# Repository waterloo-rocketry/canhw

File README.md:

## RocketCAN Hardware

This repository tracks the hardware development for the RocketCAN project. All schematics, board designs, and fabrication files are tracked in this repository. The corresponding software running on each board can be found in the `cansw_*` repositories. The CAN driver library used is tracked in the `canlib` repository.

All hardware files were developed in KiCAD.

### System Architecture

The RocketCAN project is an extension of the 2018 Flight Instrumentation project. The functions of the original Flight Instrumentation electronics are decoupled into several single-function modules connected by a Controller Area Network (CAN bus). The 2019 RocketCAN configuration consists of a radio board, an injector valve driver, a vent valve driver, a flight sensor suite, a system logger, and a GPS receiver. The modules freely share information over the CAN bus, allowing all modules to access resources such as the radio transceiver and sensor module. This minimizes the amount of component and functionality duplication, as well as power consumption (especially by the radio module). Power consumption is reduced further by allowing the radio board to control power to the rest of the system, forcing it into a low-power state while the rocket is idle. The resulting PCBs are also significantly smaller and easier to mount inside the rocket. Finally, RocketCAN’s configuration is easily extensible. A new subsystem simply needs to include a CAN communication module, after which it can communicate with all other boards on the bus. Potential extensions such as a flight computer, a state estimation module, or an air braking system would be able to use existing sensor data without implementing their own independent sensor suite.

At present, the radio board integrates with Waterloo Rocketry's Remote Launch Control System (RLCS), from which it receives instructions. It is also capable of broadcasting sensor data to RLCS.  The radio board communicates with the tower-side box of RLCS, which relays the data to the client-side box at mission control.

The CAN protocol was chosen for its high data rate, priority-based arbitration, and abundance of inexpensive hardware. The bus can safely be used by many boards at once without the risk of a low-priority message (eg. sensor data) preempting a high-priority message (eg. valve command). Microcontrollers with CAN modules, stand-alone CAN modules, and CAN transceivers are all widely available, making it cheap and simple to add CAN functionality to a subsystem.

Further descriptions and instructions for using each individual board are available in the README in the relevant board's directory.

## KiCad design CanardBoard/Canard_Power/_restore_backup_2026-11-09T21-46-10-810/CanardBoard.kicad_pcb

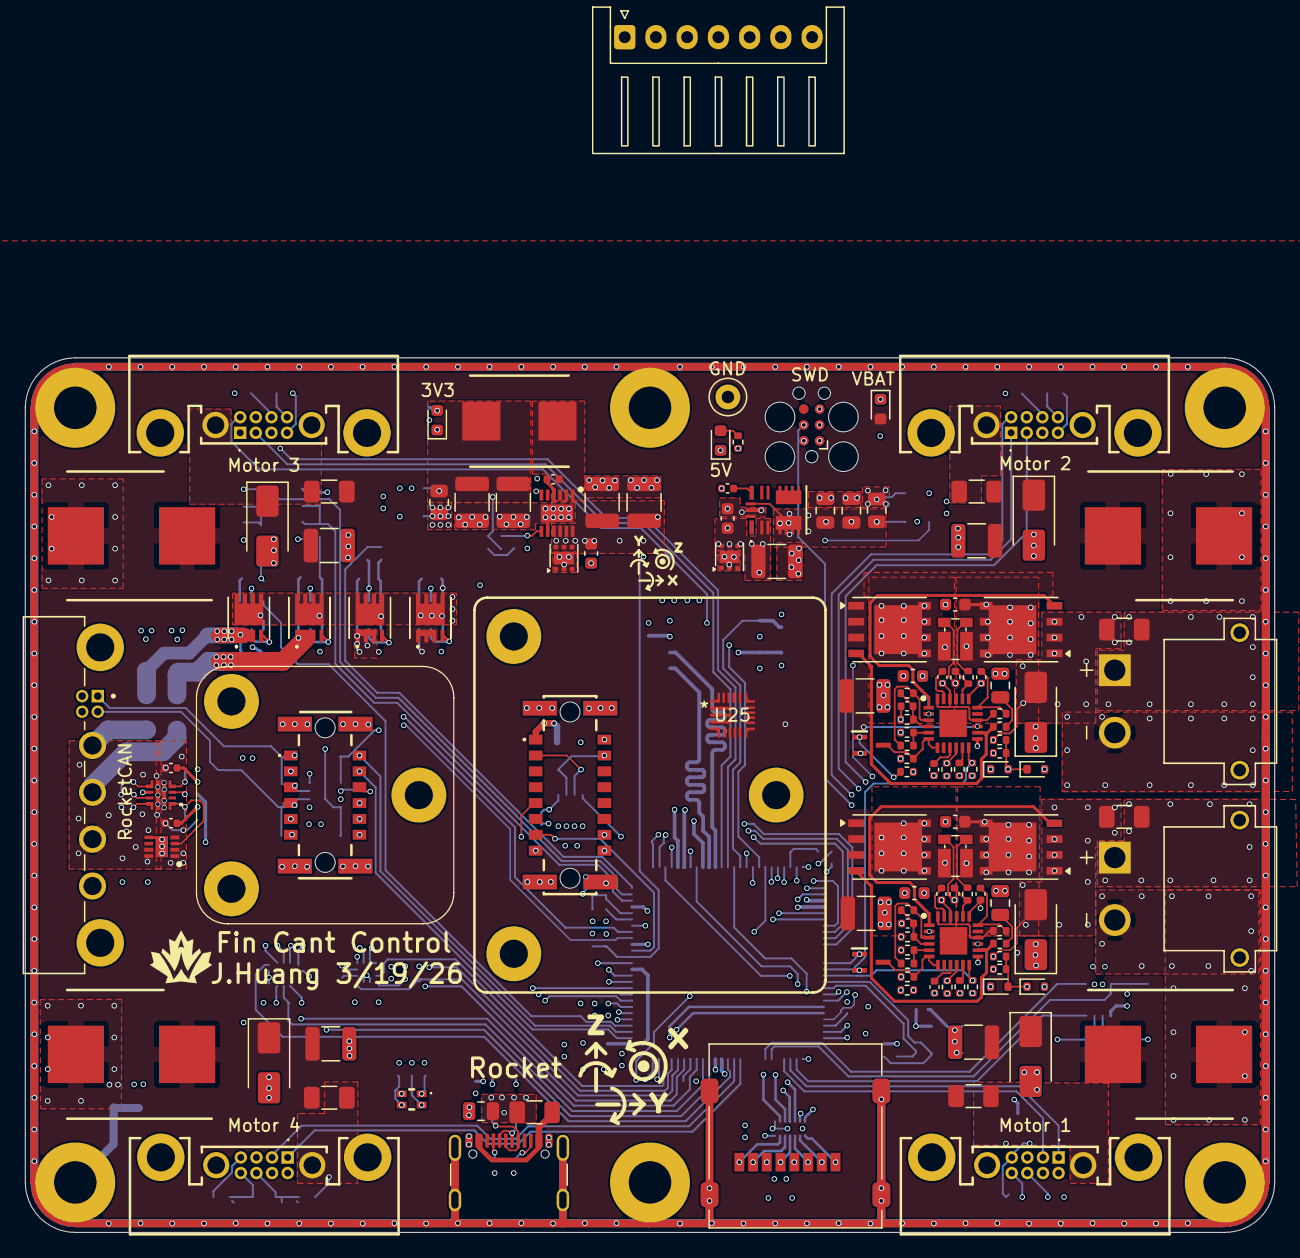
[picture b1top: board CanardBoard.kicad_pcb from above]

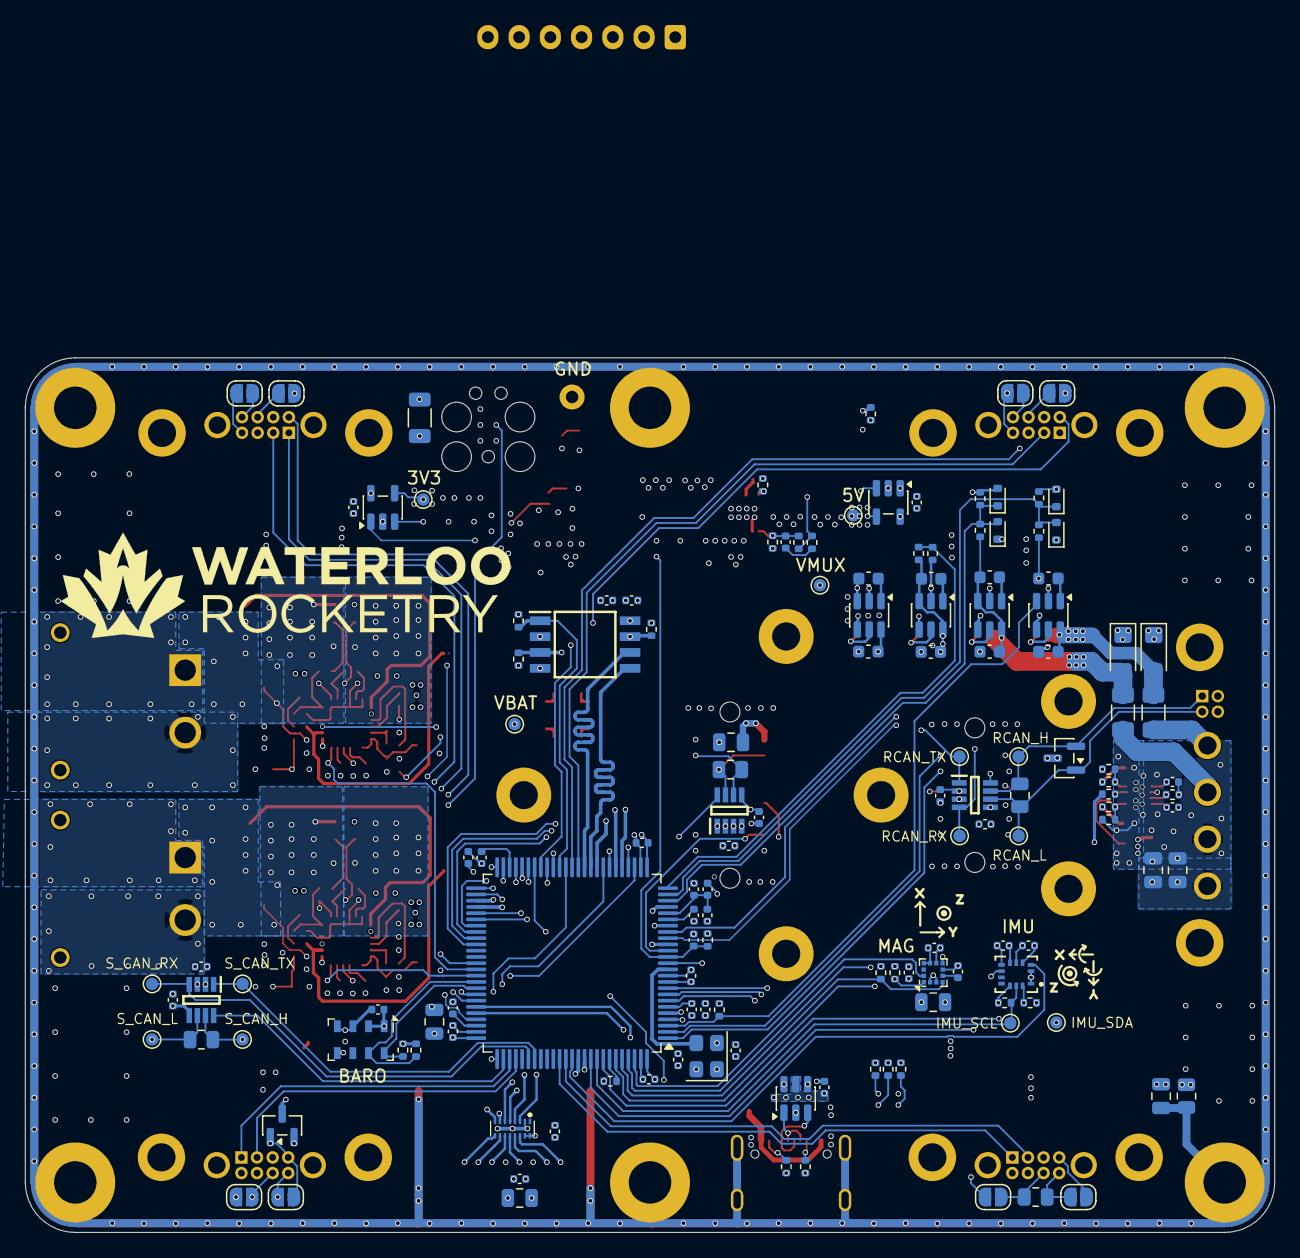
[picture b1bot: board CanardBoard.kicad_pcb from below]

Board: 6 copper layers, 100.0 x 70.0 mm, 276 parts (142 on the bottom side), 179 nets.

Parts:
C1, C6, C7, C8, C9, C10, C11, C14, C16, C18, C21, C22, C23, C24, C33, C34, C37, C40, C48, C50, C55, C57, C60, C61, C62, C66, C67, C73, C81, C82, C83, C84, C92, C93: 0.1uF; C_0402_1005Metric
C2, C4, C49: 2.2uF; C_0402_1005Metric
C3, C5, C13, C72, C91: 1uF; C_0402_1005Metric
C12, C17, C47, C56, C63, C65, C74, C76, C89: 22uF; C_0805_2012Metric
C15, C27, C28, C29, C30, C58, C59: 10nF; C_0402_1005Metric
C19, C20, C25, C26, C51, C52, C53, C54, C70, C71, C85, C86, C87, C88: 0.1uF; C_0603_1608Metric
C31, C32, C90: 0.1uF; C_0805_2012Metric
C35, C36, C38, C41, C43, C45, C68, C69, C79: 10uF; C_1210_3225Metric
C39, C42, C44, C46: 220uF; A786MW227M1HLAV011
C64: 220nF; C_0402_1005Metric
C75: 33pF; C_0402_1005Metric
C77, C78: 47uF; C_1210_3225Metric
D1: LED_RGBA; EAST1616RGBB2
D2, D3: SMAJ28CA; D_SMA
D4, D5, D6, D7, D13, D14, D15, D16: RB520S30T1G; D_SOD-523
D8, D9, D11, D12: SMAJ28A; D_SMA
D10, D17: ESDCAN01-2BLY; SOT-23
D18, D19: SMF15CA; D_SMF
D20, D21, D22: RED; LED_0603_1608Metric
F1, F2: 20A; Fuse_1206_3216Metric
F3, F4, F5, F6: 10A; Fuse_1206_3216Metric
F7, F8: 1.5A; Fuse_1206_3216Metric
F9: 5A; Fuse_1206_3216Metric
FB1: BLM15AG121SN1D; C_0402_1005Metric
H1, H2, H3, H4, H5, H6: M3; MountingHole_3.2mm_M3_Pad
J1: TagConnect_TC2030; Tag-Connect_TC2030-IDC-FP_2x03_P1.27mm_Vertical
J2: Micro_SD_Card; microSD_HC_Molex_47219-2001
J3, J4: XT30PW-M; AMASS_XT30PW-M
J5: Motor 2; G125MH10805M41AD1ADP
J6: Motor 1; G125MH10805M41AD1ADP
J7: Motor 4; G125MH10805M41AD1ADP
J8: Motor 3; G125MH10805M41AD1ADP
J9: USB_C_Receptacle_USB2.0_16P; USB_C_Receptacle_GCT_USB4105-xx-A_16P_TopMnt_Horizontal
J10: G125-MH104M4-04AD000P; connector_Harwin_G125-MH104M4-04AD000P
J11: Movella-1374028
J12: 1374027
J13: Balance Header; JST_XH_S7B-XH-A_1x07_P2.50mm_Horizontal
JP1, JP2, JP3, JP4, JP5, JP6, JP7, JP8: SolderJumper_2_Open; SolderJumper-2_P1.3mm_Open_RoundedPad1.0x1.5mm
L1: 4.7uH; SRP7050WA
Q1, Q2, Q3, Q4: SIR626DP-T1-RE3; PowerPAK_SO-8_Single
Q5, Q6: 2N7002W
Q7, Q8, Q9, Q10: 20N06D; Infineon-PG-TSDSON-8
R1, R2, R8, R14, R16, R33, R34, R37, R38, R41, R42, R47, R48, R49: 10k; R_0402_1005Metric
R3, R72, R73: 330R; R_0402_1005Metric
R4, R5, R27, R28: 100R; R_0402_1005Metric
R6, R7, R22, R24: 2.2k; R_0402_1005Metric
R9: 5.1k; R_1206_3216Metric
R13, R15, R17, R19, R21, R23, R35, R36, R39, R40, R50, R52, R54, R55, R56, R59, R61, R67: 100k; R_0402_1005Metric
R18, R20: 3.16k; R_0402_1005Metric
R25, R26, R66: 0R; R_0402_1005Metric
R29, R30: 1mR; R_Shunt_Vishay_WSKW0612
R31, R32: 10R; R_0402_1005Metric
R43, R44, R60, R65: 120R; R_0805_2012Metric
R45, R46: 5.1k; R_0402_1005Metric
R51, R53, R68: 19.1k; R_0402_1005Metric
R57: 34k; R_0402_1005Metric
R58: 681R; R_0402_1005Metric
R62: 43.2k; R_0402_1005Metric
R63, R64, R69, R74, R75: 1k; R_0402_1005Metric
R70, R71: 5m; R_0805_2012Metric
R76: 1M; R_0805_2012Metric
TP1: S_CAN_H; TestPoint_Pad_D1.0mm
TP2: S_CAN_L; TestPoint_Pad_D1.0mm
TP3: S_CAN_RX; TestPoint_Pad_D1.0mm
TP4: S_CAN_TX; TestPoint_Pad_D1.0mm
TP5: RCAN_H; TestPoint_Pad_D1.0mm
TP6: RCAN_L; TestPoint_Pad_D1.0mm
TP7: RCAN_RX; TestPoint_Pad_D1.0mm
TP8: RCAN_TX; TestPoint_Pad_D1.0mm
TP9: 3V3; TestPoint_Pad_D1.0mm
TP10: 5V; TestPoint_Pad_D1.0mm
TP11: VBAT; TestPoint_Pad_D1.0mm
TP12: VMUX; TestPoint_Pad_D1.0mm
TP13: GND; TestPoint_Loop_D2.50mm_Drill1.0mm
TP14: IMU_SCL; TestPoint_Pad_D1.0mm
TP15: IMU_SDA; TestPoint_Pad_D1.0mm
U1: STM32H733VGTx; LQFP-100_14x14mm_P0.5mm
U2: MS5611-01BA; LGA-8_3x5mm_P1.25mm
U3, U23: TVS3300DRV; WSON-6-1EP_2x2mm_P0.65mm_EP1x1.6mm
U4, U5: LM749x0
U6, U13, U16: TCAN3413DDFR
U7: USBLC6-2SC6; SOT-23-6
U8: MX25L25645GM2I-08G
U9, U10, U11, U12: LM74700; SOT-23-6
U14: TPS259472; TPS25947xx
U15: LSM303AGR; LGA-12_2x2mm_P0.5mm
U17: LMR51460
U18: TPSM33610S3QRDNRQ1; TPSM33606S3QRDNRQ1
U19, U20: INA180A3; SOT-23-5
U21: LSM6DSV32XTR
U22: EMIF06-MSD02N16; EMIF06MSD02N16
U24: TPS22975DSGR
U25: MP2759GQ-0000-P; QFN-19_MP2759_MNP
X1: ASE-4.000MHZ-L-C-T; Oscillator_SMD_Abracon_ASE-4Pin_3.2x2.5mm

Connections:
+3V3: C5.1, C6.1, C7.1, C8.1, C9.1, C10.1, C11.1, C12.1, C15.1, C16.1, C17.1, C18.1, C37.1, C40.1, C49.1, C50.1, C55.1, C57.1, C61.2, C62.2, C63.2, C66.1, C67.1, C81.2, C82.2, C83.1, C84.1, C92.1, C93.1, D1.4 (A), D4.1 (K), D6.1 (K), D13.1 (K), D15.1 (K), FB1.2, J1.1 (VCC), J2.4 (VDD), J12.A3 (3V3), J12.B4 (3V3), R1.1, R6.1, R7.1, R8.1, R33.2, R34.2, R47.1, R48.1, R49.1, R59.1, R63.2, R64.2, R70.1, R72.1, R74.1, R75.1, TP9.1 (1_1), U1.6 (VBAT), U1.11 (VDD), U1.27 (VDD), U1.50 (VDD), U1.75 (VDD), U1.100 (VDD), U2.1 (VDD), U2.2 (PS), U6.3 (VCC), U6.5 (VIO), U8.8 (VCC), U13.3 (VCC), U13.5 (VIO), U15.2 (CS_XL), U15.3 (CS_MAG), U15.9 (VDD), U15.10 (VDDIO), U16.3 (VCC), U16.5 (VIO), U19.4 (IN-), U19.5 (VS), U20.5 (VS), U21.5 (VDD_IO), U21.8 (VDD), U21.12 (CS), U22.15 (VCC), U22.16 (RDATA_VCC), X1.1 (EN), X1.4 (Vdd)
+5V: C60.1, C65.1, C91.1, J11.A1 (VIN), J12.A2 (5V), J12.B5 (5V), R61.1, R71.1, R73.1, TP10.1 (1_1), U14.5 (IN), U20.4 (IN-), U24.1 (VIN_1), U24.2 (VIN_2), U24.4 (VBIAS)
+5V_USB: C47.1, C48.1, C53.1, C87.1, F7.1, Q9.S, R54.1, U7.5 (VBUS), U11.3 (EN), U11.6 (ANODE)
+12V_RKT: C52.1, C86.1, D18.2 (A2), F9.2, Q8.S, R52.1, U10.3 (EN), U10.6 (ANODE)
+VBAT: C35.1, C36.1, C38.1, C39.1, C41.1, C42.1, C43.1, C44.1, C45.1, C46.1, C54.1, C88.1, D8.1 (A1), D9.1 (A1), D11.1 (A1), D12.1 (A1), D22.2 (A), F3.2, F4.2, F5.2, F6.2, Q3.S, Q4.S, Q10.S, TP11.1 (1_1), U4.15 (OUT), U5.15 (OUT), U12.3 (EN), U12.6 (ANODE)
+VCHG: C51.1, C85.1, D19.2 (A2), F8.2, Q7.S, R50.1, U9.6 (ANODE), U25.10 (CELL)
+VMUX: C68.2, C69.2, C70.2, C71.2, C79.2, Q7.D, Q8.D, Q9.D, Q10.D, TP12.1 (1_1), U3.4 (IN), U3.5 (IN), U3.6 (IN), U9.4 (CATHODE), U10.4 (CATHODE), U11.4 (CATHODE), U12.4 (CATHODE), U17.9 (EN), U17.10 (VIN_1), U17.11 (VIN_2), U17.12 (VIN_3), U18.2 (EN), U18.3 (VIN), U23.4 (IN), U23.5 (IN), U23.6 (IN)
/32G IMU/IMU_INT1: U1.88 (PD7), U21.4 (INT1)
/32G IMU/IMU_INT2: U1.91 (PB5), U21.9 (INT2)
/32G IMU/IMU_SCL: R75.2, TP14.1 (1_1), U1.92 (PB6), U21.13 (SCL)
/32G IMU/IMU_SDA: R74.2, TP15.1 (1_1), U1.93 (PB7), U21.14 (SDA)
/AD Breakout/ADC_INT: J12.A6 (ADC_ALERT), U1.42 (PE12)
/AD Breakout/ADI_SCL: J12.A4 (SCL), U1.46 (PB10)
/AD Breakout/ADI_SDA: J12.A5 (SDA), U1.47 (PB11)
/AD Breakout/ADXL_INT: J12.B3 (ACCEL_INT), U1.45 (PE15)
/AD Breakout/ADXRS_ST1: J12.B2 (ST1), U1.1 (PE2)
/AD Breakout/ADXRS_ST2: J12.B1 (ST2), U1.2 (PE3)
/Barometer/BAR_SCL: R6.2, U1.67 (PA8), U2.8 (SCLK)
/Barometer/BAR_SDA: R7.2, U1.66 (PC9), U2.7 (SDI/SDA)
/Flash/FLASH_CLK: U1.36 (PB2), U8.6 (SCLK)
/Flash/FLASH_CS: R47.2, U1.40 (PE10), U8.1 (CS#)
/Flash/FLASH_IO0: U1.35 (PB1), U8.5 (SI/SIO0)
/Flash/FLASH_IO1: U1.34 (PB0), U8.2 (SO/SIO1)
/Flash/FLASH_IO2: R48.2, U1.31 (PA7), U8.3 (WP#/SIO2)
/Flash/FLASH_IO3: R49.2, U1.30 (PA6), U8.7 (RESET#/SIO3)
/Magnetometer/INT1_MAG_ACCEL: U1.98 (PE1), U15.12 (INT_1_XL)
/Magnetometer/INT_MAG: U1.97 (PE0), U15.7 (INT_MAG/DRDY)
/Magnetometer/MAG_SCL: R64.1, U1.95 (PB8), U15.1 (SCL/SPC)
/Magnetometer/MAG_SDA: R63.1, U1.96 (PB9), U15.4 (SDA/SDI/SDO)
/Movella/MCAN_H: J11.A2 (CAN_H), R65.2, U16.7 (CANH)
/Movella/MCAN_L: J11.B2 (CAN_L), R65.1, U16.6 (CANL)
/Power Input/BAT1_IN: C19.1, D2.2 (A2), F1.1, Q1.S, R13.1, R39.1, U4.2 (A)
/Power Input/BAT2_IN: C20.1, D3.2 (A2), F2.1, Q2.S, R15.1, R40.1, U5.2 (A)
/Power Input/BAT_FLT1: R33.1, U1.64 (PC7), U4.12 (~FLT)
/Power Input/BAT_FLT2: R34.1, U1.65 (PC8), U5.12 (~FLT)
/Power Input/ISENS_BAT1: R37.1, U1.29 (PA5), U4.10 (IMON)
/Power Input/ISENS_BAT2: R38.1, U1.28 (PA4), U5.10 (IMON)
/Power Input/PWR_EN: Q5.1 (G), Q6.1 (G), R41.2, R42.2, U1.63 (PC6)
/Power Input/VSENS_BAT1: D4.2 (A), D5.1 (K), R13.2, R14.1, U1.32 (PC4)
/Power Input/VSENS_BAT2: D6.2 (A), D7.1 (K), R15.2, R16.1, U1.33 (PC5)
/Power Muxing/CHG_MUX_EN: R8.2, U1.3 (PE4), U9.3 (EN)
/Power Muxing/VSENS_CHG: D13.2 (A), D14.1 (K), R50.2, R51.2, U1.24 (PA2)
/Power Muxing/VSENS_RKT: D15.2 (A), D16.1 (K), R52.2, R53.2, U1.23 (PA1)
/Power Muxing/VSENS_USB: R54.2, R55.2, U1.25 (PA3)
/Power Rails/ISENS_3V3: U1.17 (PC2_C), U19.1 (VO)
/Power Rails/ISENS_5V: U1.18 (PC3_C), U20.1 (VO)
/Processor/EN_EXT_5V: R61.2, R62.1, U1.4 (PE5), U14.1 (EN/UVLO), U24.3 (ON)
/Processor/LED_B: R5.2, U1.9 (PC15)
/Processor/LED_G: R4.2, U1.8 (PC14)
/Processor/LED_R: R3.2, U1.7 (PC13)
/Processor/NRST: C1.1, J1.3 (~RESET), R1.2, U1.14 (NRST)
/Processor/PG_EXT_5V: R59.2, U1.5 (PE6), U14.3 (PG)
/Processor/PWM1: J6.5, U1.39 (PE9)
/Processor/PWM2: J5.5, U1.41 (PE11)
/Processor/PWM3: J8.5, U1.43 (PE13)
/Processor/PWM4: J7.5, U1.44 (PE14)
/Processor/RCAN_RX: TP7.1 (1_1), U1.59 (PD12), U13.4 (RXD)
/Processor/RCAN_STB: U1.58 (PD11), U13.8 (STB)
/Processor/RCAN_TX: TP8.1 (1_1), U1.60 (PD13), U13.1 (TXD)
/Processor/RCC_osc_In: U1.12 (PH0), X1.3 (OUT)
/Processor/SD_CLK: U1.16 (PC1), U22.5 (CLK_IN)
/Processor/SD_CMD: U1.22 (PA0), U22.6 (CMD_IN)
/Processor/SD_D0: U1.53 (PB14), U22.4 (DAT0_IN)
/Processor/SD_D1: U1.54 (PB15), U22.3 (DAT1_IN)
/Processor/SD_D2: U1.89 (PB3(JTDO), U22.8 (DAT2_IN)
/Processor/SD_D3: U1.90 (PB4(NJTRST)), U22.7 (DAT3_IN)
/Processor/SERVO1_RX: J6.2, U1.79 (PC11)
/Processor/SERVO1_TX: J6.1, U1.78 (PC10)
/Processor/SERVO2_RX: J5.2, U1.69 (PA10)
/Processor/SERVO2_TX: J5.1, U1.68 (PA9)
/Processor/SERVO3_RX: J8.2, U1.37 (PE7)
/Processor/SERVO3_TX: J8.1, U1.38 (PE8)
/Processor/SERVO4_RX: J7.2, U1.87 (PD6)
/Processor/SERVO4_TX: J7.1, U1.86 (PD5)
/Processor/S_CAN_RX: TP3.1 (1_1), U1.81 (PD0), U6.4 (RXD)
/Processor/S_CAN_STB: U1.77 (PA15(JTDI)), U6.8 (STB)
/Processor/S_CAN_TX: TP4.1 (1_1), U1.82 (PD1), U6.1 (TXD)
/Processor/USB_D+: U1.71 (PA12), U7.4 (I/O2)
/Processor/USB_D-: U1.70 (PA11), U7.6 (I/O1)
/Processor/VCAP1: C2.2, U1.48 (VCAP)
/Processor/VCAP2: C4.2, U1.73 (VCAP)
/Processor/VDDA: C13.1, C14.1, FB1.1, U1.21 (VDDA)
/RocketCAN/RCAN_H: D17.2 (K), J10.1 (CANH), R60.2, TP5.1 (1_1), U13.7 (CANH)
/RocketCAN/RCAN_L: D17.1 (K), J10.2 (CANL), R60.1, TP6.1 (1_1), U13.6 (CANL)
/RocketCAN/RKT_5V_OUT: C56.1, C89.1, J10.C (+5V), R56.1, U14.6 (OUT), U24.7 (VOUT_1), U24.8 (VOUT_2)
/SD_Card/CLK_CARD: J2.5 (CLK), U22.12 (CLK_EX)
/SD_Card/CMD_CARD: J2.3 (CMD), U22.11 (CMD_EX)
/SD_Card/DAT0_CARD: J2.7 (DAT0), U22.13 (DAT0_EX)
/SD_Card/DAT1_CARD: J2.8 (DAT1), U22.14 (DAT1_EX)
/SD_Card/DAT2_CARD: J2.1 (DAT2), U22.9 (DAT2_EX)
/SD_Card/DAT3_CARD: J2.2 (DAT3/CD), U22.10 (DAT3_EX)
/Servos/CANH_4: J7.7, JP3.2 (B), R44.1
/Servos/CANH_12: J5.3, J6.7, JP1.2 (B), JP7.1 (A)
/Servos/CANH_23: J5.7, J8.3, JP5.1 (A), JP7.2 (B)
/Servos/CANH_34: J7.3, J8.7, JP3.1 (A), JP5.2 (B)
/Servos/CANL_4: J7.8, JP4.2 (B), R44.2
/Servos/CANL_12: J5.4, J6.8, JP2.2 (B), JP8.1 (A)
/Servos/CANL_23: J5.8, J8.4, JP6.1 (A), JP8.2 (B)
/Servos/CANL_34: J7.4, J8.8, JP4.1 (A), JP6.2 (B)
/Servos/S_CAN_H: D10.2 (K), J6.3, JP1.1 (A), R43.2, TP1.1 (1_1), U6.7 (CANH)
/Servos/S_CAN_L: D10.1 (K), J6.4, JP2.1 (A), R43.1, TP2.1 (1_1), U6.6 (CANL)
GND: C1.2, C2.1, C3.2, C4.1, C5.2, C6.2, C7.2, C8.2, C9.2, C10.2, C11.2, C12.2, C13.2, C14.2, C15.2, C16.2, C17.2, C18.2, C19.2, C20.2, C21.2, C22.2, C25.2, C26.2, C31.2, C32.2, C33.2, C34.2, C35.2, C36.2, C37.2, C38.2, C39.2, C40.2, C41.2, C42.2, C43.2, C44.2, C45.2, C46.2, C47.2, C48.2, C49.2, C50.2, C55.2, C56.2, C57.2, C58.2, C59.2, C60.2, C61.1, C62.1, C63.1, C64.1, C65.2, C66.2, C67.2, C68.1, C69.1, C70.1, C71.1, C72.1, C74.1, C76.1, C77.1, C78.1, C79.1, C81.1, C82.1, C83.2, C84.2, C85.2, C86.2, C87.2, C88.2, C89.2, C90.2, C91.2, C92.2, C93.2, D2.1 (A1), D3.1 (A1), D5.2 (A), D7.2 (A), D8.2 (A2), D9.2 (A2), D10.3 (A), D11.2 (A2), D12.2 (A2), D14.2 (A), D16.2 (A), D17.3 (A), D18.1 (A1), D19.1 (A1), D20.1 (K), D21.1 (K), J1.5 (GND), J2.6 (VSS), J3.N, J4.N, J5.6, J5.10 (A2), J6.6, J6.10 (A2), J7.6, J7.10 (A2), J8.6, J8.10 (A2), J9.A1 (GND), J9.A12 (GND), J9.B1 (GND), J9.B12 (GND), J10.D (GND), J11.B1 (GND), J11.B7 (GND), J11.MP1, J11.MP2, J11.MP3, J11.MP4, J12.A1 (GND), J12.B6 (GND), J12.MP1, J12.MP2, J12.MP3, J12.MP4, Q5.2 (S), Q6.2 (S), R2.2, R9.2, R14.2, R16.2, R18.2, R20.2, R22.2, R24.2, R35.2, R36.2, R37.2, R38.2, R41.1, R42.1, R45.2, R46.2, R51.1, R53.1, R55.1, R57.2, R58.2, R62.2, R66.1, R68.1, R76.2, TP13.1 (1_1), U1.10 (VSS), U1.19 (VSSA), U1.26 (VSS), U1.49 (VSS), U1.74 (VSS), U1.99 (VSS), U2.3 (GND), U2.4 (CSB), U2.5 (CSB), U3.1 (GND), U3.2 (GND), U3.3 (GND), U3.7 (GND), U4.13 (GND), U5.13 (GND), U6.2 (GND), U7.2 (GND), U8.4 (GND), U9.2 (GND), U10.2 (GND), U11.2 (GND), U12.2 (GND), U13.2 (GND), U14.8 (GND), U15.6 (GND), U15.8 (GND), U16.2 (GND), U17.8 (AGND), U17.13 (PGND/DAP), U18.10 (GND), U18.11 (MODE/SYNCH), U19.2 (GND), U20.2 (GND), U21.1 (SDO/SA0), U21.2 (SDX/AH1/QVAR1), U21.3 (SCX/AH2/QVAR2), U21.6 (GND), U21.7 (GND), U22.2 (RDAT3_GND), U22.17 (EP_(GND)), U23.1 (GND), U23.2 (GND), U23.3 (GND), U23.7 (GND), U24.5 (GND), U24.9 (EP), U25.6 (PGND), U25.7 (PGND), U25.16 (AGND), X1.2 (GND)
unnamed: C31.1, R31.2
unnamed: C32.1, R32.2
unnamed: C75.2, R69.1
unnamed: D1.3 (BK), R5.1
unnamed: D1.2 (GK), R4.1
unnamed: D1.1 (RK), R3.1
unnamed: D20.2 (A), R72.2
unnamed: D21.2 (A), R73.2
unnamed: D22.1 (K), R9.1
unnamed: F1.2, J3.P
unnamed: F2.2, J4.P
unnamed: F7.2, J9.A4 (VBUS), J9.A9 (VBUS), J9.B4 (VBUS), J9.B9 (VBUS)
unnamed: J1.4 (SWCLK), U1.76 (PA14(JTCK)
unnamed: J1.2 (SWDIO), U1.72 (PA13(JTMS)
unnamed: F3.1, J5.9 (A1)
unnamed: F4.1, J6.9 (A1)
unnamed: F5.1, J7.9 (A1)
unnamed: F6.1, J8.9 (A1)
unnamed: J9.A5 (CC1), R46.1
unnamed: J9.B5 (CC2), R45.1
unnamed: J9.A6 (D+), J9.B6 (D+), U7.3 (I/O2)
unnamed: J9.A7 (D-), J9.B7 (D-), U7.1 (I/O1)
unnamed: F9.1, J10.B (+12V)
unnamed: F8.1, J10.A (+CHG)
unnamed: Q3.D, R29.1
unnamed: Q4.D, R30.1
unnamed: Q5.3 (D), R39.2, U4.6 (EN), U4.7 (~SLEEP)
unnamed: Q6.3 (D), R40.2, U5.6 (EN), U5.7 (~SLEEP)
unnamed: R27.1, R29.3
unnamed: R28.1, R30.3
unnamed: R2.1, U1.94 (BOOT0)
unnamed: C3.1, U1.20 (VREF+)
unnamed: C23.1, C25.1, Q1.D, R25.1, R29.4, U4.16 (SLEEP_OV), U4.22 (VS), U4.24 (C)
unnamed: C23.2, U4.23 (CAP)
unnamed: C27.1, R27.2, U4.20 (CS+)
unnamed: C27.2, C28.2, R29.2, U4.19 (CS-)
unnamed: Q1.G, U4.1 (DGATE)
unnamed: Q3.G, R31.1, U4.14 (HGATE)
unnamed: R35.1, U4.11 (ILIM)
unnamed: C28.1, R25.2, U4.18 (ISCP)
unnamed: R21.2, R22.1, U4.5 (OV)
unnamed: R17.1, R21.1, U4.3 (SW)
unnamed: C33.1, U4.9 (TMR)
unnamed: C21.1, R17.2, R18.1, U4.4 (UVLO)
unnamed: C24.1, C26.1, Q2.D, R26.1, R30.4, U5.16 (SLEEP_OV), U5.22 (VS), U5.24 (C)
unnamed: C24.2, U5.23 (CAP)
unnamed: C29.1, R28.2, U5.20 (CS+)
unnamed: C29.2, C30.2, R30.2, U5.19 (CS-)
unnamed: Q2.G, U5.1 (DGATE)
unnamed: Q4.G, R32.1, U5.14 (HGATE)
unnamed: R36.1, U5.11 (ILIM)
unnamed: C30.1, R26.2, U5.18 (ISCP)
unnamed: R23.2, R24.1, U5.5 (OV)
unnamed: R19.1, R23.1, U5.3 (SW)
unnamed: C34.1, U5.9 (TMR)
unnamed: C22.1, R19.2, R20.1, U5.4 (UVLO)
unnamed: Q7.G, U9.5 (GATE)
unnamed: C51.2, U9.1 (VCAP)
unnamed: Q8.G, U10.5 (GATE)
unnamed: C52.2, U10.1 (VCAP)
unnamed: Q9.G, U11.5 (GATE)
unnamed: C53.2, U11.1 (VCAP)
unnamed: Q10.G, U12.5 (GATE)
unnamed: C54.2, U12.1 (VCAP)
unnamed: C58.1, U14.7 (DVDT)
unnamed: R58.1, U14.9 (ILM)
unnamed: C59.1, U14.10 (ITIMER)
unnamed: R56.2, R57.1, U14.4 (PGTH)
unnamed: C64.2, U15.5 (C1)
unnamed: C73.2, U17.4 (BOOT)
unnamed: C75.1, R67.1, R68.2, U17.7 (FB)
unnamed: R66.2, U17.6 (RT)
unnamed: C73.1, L1.1, U17.1 (SW_1), U17.2 (SW_2), U17.3 (SW_3)
unnamed: C74.2, C76.2, R70.2, U18.4 (VOUT), U18.9 (FB), U19.3 (IN+)
unnamed: C72.2, U18.8 (VCC)
unnamed: C77.2, C78.2, L1.2, R67.2, R69.2, R71.2, U20.3 (IN+)
SHIELD: C90.1, H1.1 (1_1), H2.1 (1_1), H3.1 (1_1), H4.1 (1_1), H5.1 (1_1), H6.1 (1_1), J2.9 (SHIELD), J9.S1 (SHIELD), R76.1

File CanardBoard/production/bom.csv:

Designator,Footprint,Quantity,Value,LCSC Part #
"C1, C10, C11, C14, C16, C18, C21, C22, C23, C24, C33, C34, C37, C40, C48, C50, C55, C57, C6, C60, C61, C62, C66, C67, C7, C73, C8, C81, C82, C83, C84, C9, C92, C93",0402,34,0.1uF,C85858
"C12, C17, C47, C56, C63, C65, C74, C76, C89",0805,9,22uF,C86816
"C13, C3, C5, C72, C91",0402,5,1uF,C77007
"C15, C27, C28, C29, C30, C58, C59",0402,7,10nF,C91601
"C19, C20, C25, C26, C51, C52, C53, C54, C70, C71, C85, C86, C87, C88",0603,14,0.1uF,C3011652
"C2, C4, C49",0402,3,2.2uF,C77002
"C31, C32, C90",0805,3,0.1uF,C882587
"C35, C36, C38, C41, C43, C45, C68, C69, C79",1210,9,10uF,C77102
"C39, C42, C44, C46",A786MW227M1HLAV011,4,220uF,A786MW227M1HLAV011
C64,0402,1,220nF,C126524
C75,0402,1,33pF,C126506
"C77, C78",1210,2,47uF,C77101
D1,EAST1616RGBB2,1,LED_RGBA,C6606484
"D10, D17",SOT-23,2,ESDCAN01-2BLY,C1976606
"D11, D12, D8, D9",D_SMA,4,SMAJ28A,C148227
"D13, D14, D15, D16, D4, D5, D6, D7",D_SOD-523,8,RB520S30T1G,C154821
"D18, D19",D_SMF,2,SMF15CA,C1851361
"D2, D3",D_SMA,2,SMAJ28CA,C148228
"D20, D21, D22",0603,3,RED,C2986060
"F1, F2",1206,2,20A,C2838910
"F3, F4, F5, F6",1206,4,10A,C41367232
"F7, F8",1206,2,1.5A,C883133
F9,1206,1,5A,C41367229
FB1,0402,1,BLM15AG121SN1D,C85812
J10,connector_Harwin_G125-MH104M4-04AD000P,1,G125-MH104M4-04AD000P,
J11,Movella-1374028,1,Movella-1374028,
J12,1374027,1,1374027,
J2,microSD_HC_Molex_47219-2001,1,Micro_SD_Card,C164170
"J3, J4",AMASS_XT30PW-M,2,XT30PW-M,
J5,G125MH10805M41AD1ADP,1,Motor 2,
J6,G125MH10805M41AD1ADP,1,Motor 1,
J7,G125MH10805M41AD1ADP,1,Motor 4,
J8,G125MH10805M41AD1ADP,1,Motor 3,
J9,USB_C_Receptacle_GCT_USB4105-xx-A_16P_TopMnt_Horizontal,1,USB_C_Receptacle_USB2.0_16P,C165948
L1,SRP7050WA,1,4.7uH,C19947706
"Q1, Q2, Q3, Q4",PowerPAK_SO-8_Single,4,SIR626DP-T1-RE3,
"Q10, Q7, Q8, Q9",Infineon-PG-TSDSON-8,4,20N06D,C7543835
"Q5, Q6",2N7002W,2,2N7002W,C232391
"R1, R14, R16, R2, R33, R34, R37, R38, R41, R42, R47, R48, R49, R8",0402,14,10k,C144807
"R13, R15, R17, R19, R21, R23, R35, R36, R39, R40, R50, R52, R54, R55, R56, R59, R61, R67",0402,18,100k,C144809
"R18, R20",0402,2,3.16k,C227034
"R22, R24, R6, R7",0402,4,2.2k,C144773
"R25, R26",0402,2,0R,C226739
"R27, R28, R4, R5",0402,4,100R,C144808
"R29, R30",R_Shunt_Vishay_WSKW0612,2,1mR,C1517439
"R3, R72, R73",0402,3,330R,C226996
"R31, R32",0402,2,10R,C144805
"R43, R44, R65",0805,3,120R,C727984
"R45, R46",0402,2,5.1k,C144745
"R51, R53, R68",0402,3,19.1k,C226835
R57,0402,1,34k,C227006
R58,0402,1,681R,C416567
R62,0402,1,43.2k,C278596
"R63, R64, R69, R74, R75",0402,5,1k,C144789
"R70, R71",0805,2,5m,C728267
R76,0805,1,1M,C228604
R9,1206,1,5.1k,C229719
U1,LQFP-100_14x14mm_P0.5mm,1,STM32H733VGTx,
"U10, U11, U12, U9",SOT-23-6,4,LM74700,
"U13, U16, U6",TCAN3413DDFR,3,TCAN3413DDFR,
U14,TPS25947xx,1,TPS259472,C3662789
U15,LGA-12_2x2mm_P0.5mm,1,LSM303AGR,
U17,LMR51460,1,LMR51460,C41802645
U18,TPSM33606S3QRDNRQ1,1,TPSM33610S3QRDNRQ1,
"U19, U20",SOT-23-5,2,INA180A3,C122882
U2,LGA-8_3x5mm_P1.25mm,1,MS5611-01BA,
U21,LSM6DSV32XTR,1,LSM6DSV32XTR,
U22,EMIF06MSD02N16,1,EMIF06-MSD02N16,C5267594
"U23, U3",WSON-6-1EP_2x2mm_P0.65mm_EP1x1.6mm,2,TVS3300DRV,C2863624
"U4, U5",LM749x0,2,LM749x0,
U7,SOT-23-6,1,USBLC6-2SC6,C7519
U8,MX25L25645GM2I-08G,1,MX25L25645GM2I-08G,
X1,Oscillator_SMD_Abracon_ASE-4Pin_3.2x2.5mm,1,ASE-4.000MHZ-L-C-T,C437121

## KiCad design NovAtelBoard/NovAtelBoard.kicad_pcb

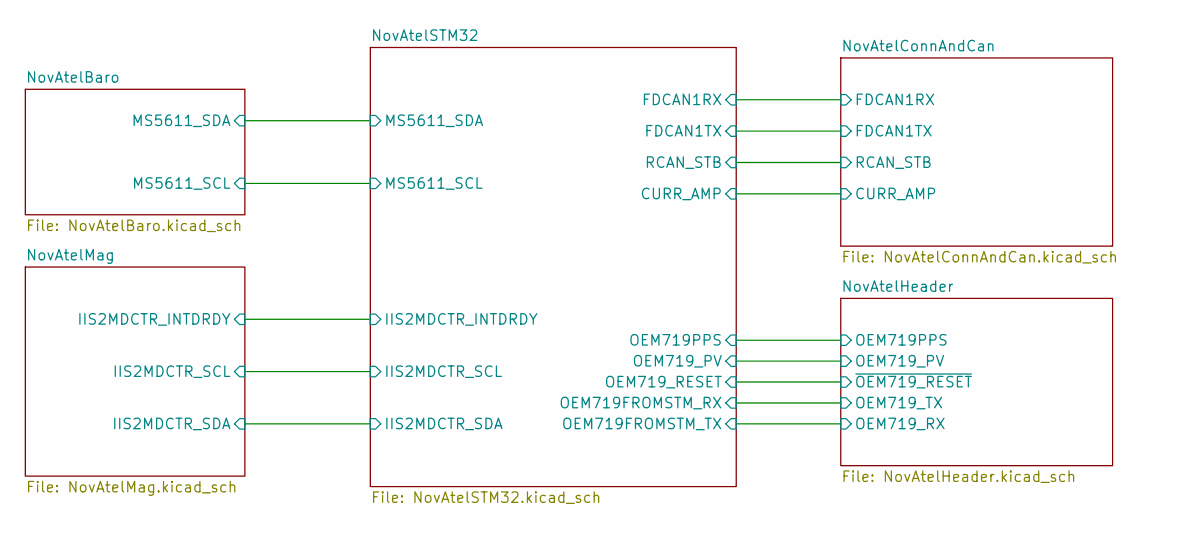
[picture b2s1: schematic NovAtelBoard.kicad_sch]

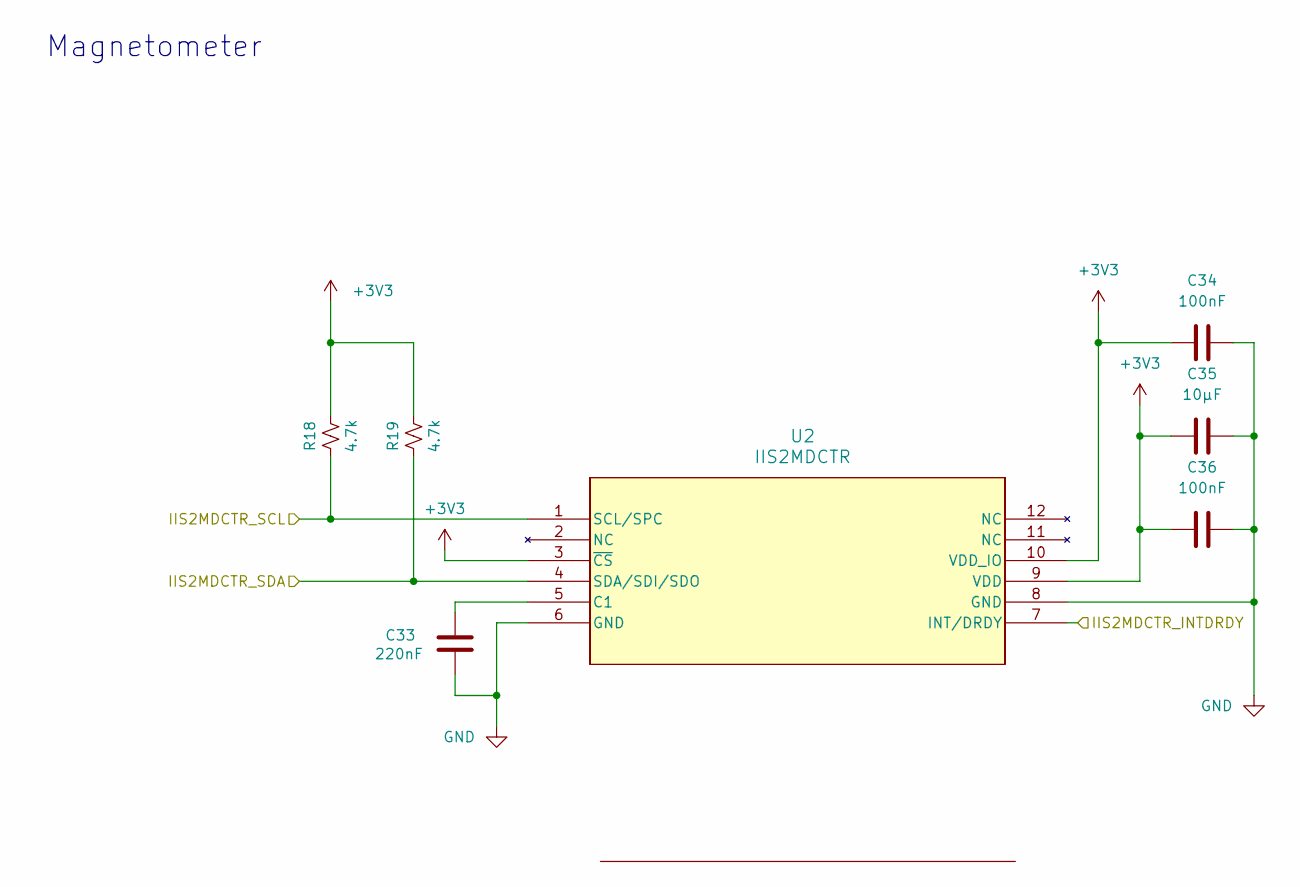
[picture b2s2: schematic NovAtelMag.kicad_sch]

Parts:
C33: 220nF; C_0603_1608Metric_Pad1.08x0.95mm_HandSolder
C34, C36: 100nF; C_0603_1608Metric_Pad1.08x0.95mm_HandSolder
C35: 10μF; C_0603_1608Metric_Pad1.08x0.95mm_HandSolder
R18, R19: 4.7k; R_0402_1005Metric; LCSC Part # C144773
U2: IIS2MDCTR; LGA-12_2X2X0P7_STM

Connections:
+3V3: C34.1, C35.2, C36.2, R18.1, R19.1, U2.3 (~CS), U2.9 (VDD), U2.10 (VDD_IO); also elsewhere on the board
/NovAtelMag/IIS2MDCTR_INTDRDY: U2.7 (INT/DRDY); also elsewhere on the board
/NovAtelMag/IIS2MDCTR_SCL: R18.2, U2.1 (SCL/SPC); also elsewhere on the board
/NovAtelMag/IIS2MDCTR_SDA: R19.2, U2.4 (SDA/SDI/SDO); also elsewhere on the board
GND: C33.1, C34.2, C35.1, C36.1, U2.6 (GND), U2.8 (GND); also elsewhere on the board
unnamed: C33.2, U2.5 (C1)

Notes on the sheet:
Magnetometer

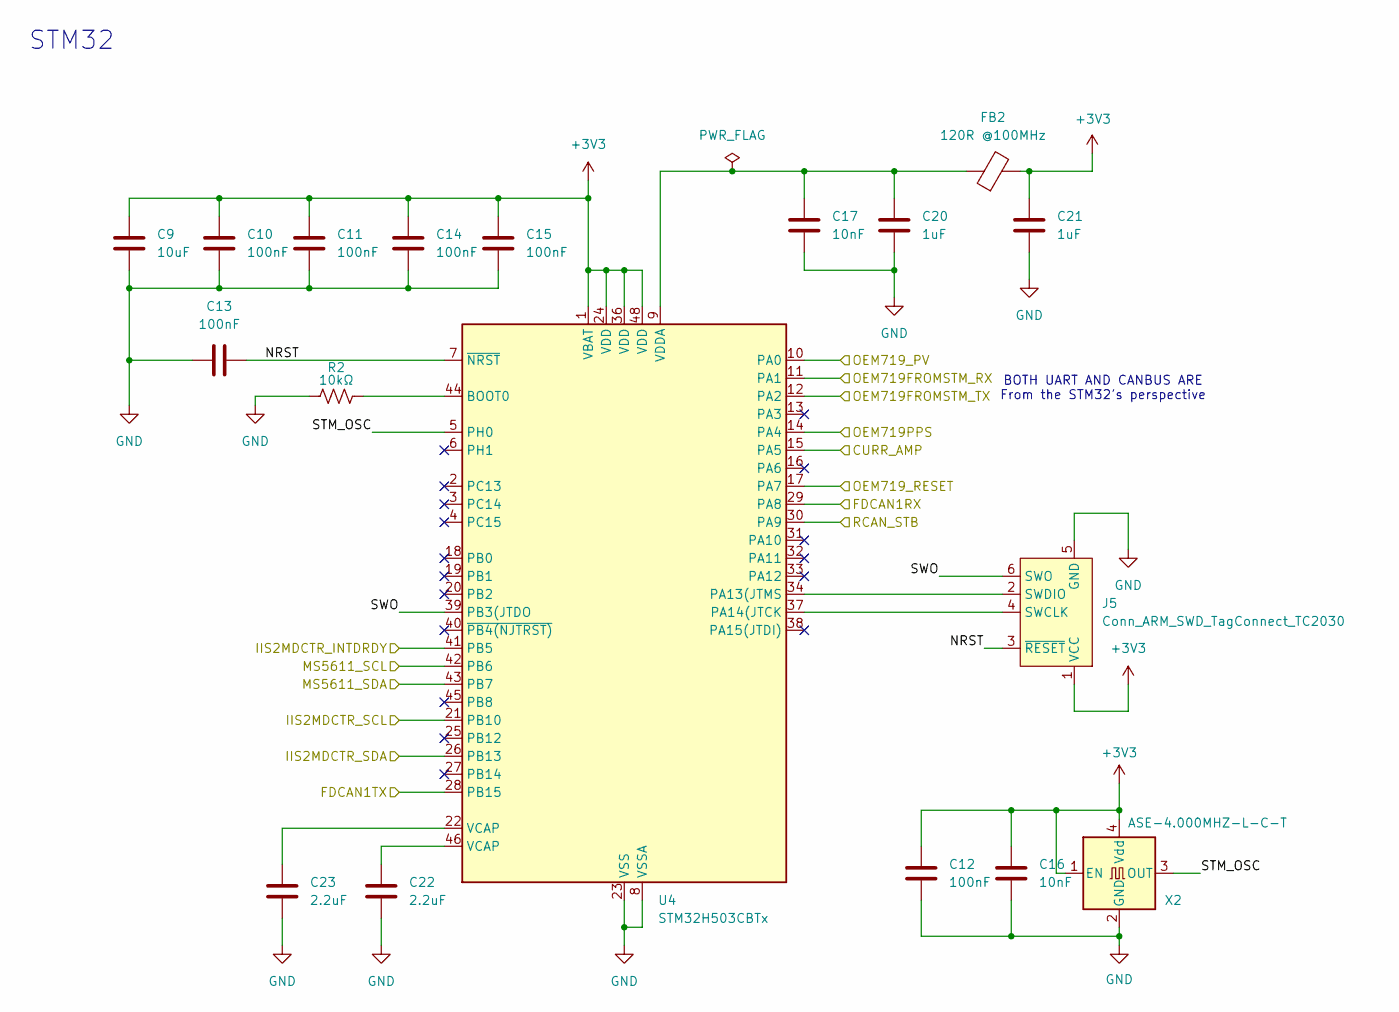
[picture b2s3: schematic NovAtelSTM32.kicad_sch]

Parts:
C9: 10uF; C_0603_1608Metric_Pad1.08x0.95mm_HandSolder
C10, C11, C12, C13, C14, C15: 100nF; C_0603_1608Metric_Pad1.08x0.95mm_HandSolder
C16, C17: 10nF; C_0603_1608Metric_Pad1.08x0.95mm_HandSolder
C20, C21: 1uF; C_0603_1608Metric_Pad1.08x0.95mm_HandSolder
C22, C23: 2.2uF; C_0603_1608Metric_Pad1.08x0.95mm_HandSolder
FB2: 120R @100MHz
J5: Conn_ARM_SWD_TagConnect_TC2030; Tag-Connect_TC2030-IDC-FP_2x03_P1.27mm_Vertical
R2: 10kΩ; R_Array_SIP4
U4: STM32H503CBTx; LQFP-48_7x7mm_P0.5mm
X2: ASE-4.000MHZ-L-C-T; Oscillator_SMD_Abracon_ASE-4Pin_3.2x2.5mm; LCSC Part # C437121

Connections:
+3V3: C9.1, C10.1, C11.1, C12.1, C14.1, C15.1, C16.1, C21.1, FB2.2, J5.1 (VCC), U4.1 (VBAT), U4.24 (VDD), U4.36 (VDD), U4.48 (VDD), X2.1 (EN), X2.4 (Vdd); also elsewhere on the board
/NovAtelBaro/MS5611_SCL: U4.42 (PB6); also elsewhere on the board
/NovAtelBaro/MS5611_SDA: U4.43 (PB7); also elsewhere on the board
/NovAtelConnAndCan/CURR_AMP: U4.15 (PA5); also elsewhere on the board
/NovAtelConnAndCan/FDCAN1RX: U4.29 (PA8); also elsewhere on the board
/NovAtelConnAndCan/FDCAN1TX: U4.28 (PB15); also elsewhere on the board
/NovAtelConnAndCan/RCAN_STB: U4.30 (PA9); also elsewhere on the board
/NovAtelHeader/OEM719PPS: U4.14 (PA4); also elsewhere on the board
/NovAtelHeader/OEM719_PV: U4.10 (PA0); also elsewhere on the board
/NovAtelHeader/OEM719_RX: U4.12 (PA2); also elsewhere on the board
/NovAtelHeader/OEM719_TX: U4.11 (PA1); also elsewhere on the board
/NovAtelHeader/~OEM719_RESET: U4.17 (PA7); also elsewhere on the board
/NovAtelMag/IIS2MDCTR_INTDRDY: U4.41 (PB5); also elsewhere on the board
/NovAtelMag/IIS2MDCTR_SCL: U4.21 (PB10); also elsewhere on the board
/NovAtelMag/IIS2MDCTR_SDA: U4.26 (PB13); also elsewhere on the board
/NovAtelSTM32/NRST: C13.1, J5.3 (~RESET), U4.7 (~NRST)
/NovAtelSTM32/STM_OSC: U4.5 (PH0), X2.3 (OUT)
/NovAtelSTM32/SWO: J5.6 (SWO), U4.39 (PB3(JTDO)
GND: C9.2, C10.2, C11.2, C12.2, C13.2, C14.2, C15.2, C16.2, C17.2, C20.2, C21.2, C22.2, C23.2, J5.5 (GND), R2.1, U4.8 (VSSA), U4.23 (VSS), U4.35 (VSS), U4.47 (VSS), X2.2 (GND); also elsewhere on the board
unnamed: C22.1, U4.46 (VCAP)
unnamed: C23.1, U4.22 (VCAP)
unnamed: J5.4 (SWCLK), U4.37 (PA14(JTCK)
unnamed: J5.2 (SWDIO), U4.34 (PA13(JTMS)
unnamed: R2.2, U4.44 (BOOT0)
unnamed: C17.1, C20.1, FB2.1, U4.9 (VDDA)

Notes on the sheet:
STM32
BOTH UART AND CANBUS ARE From the STM32's perspective

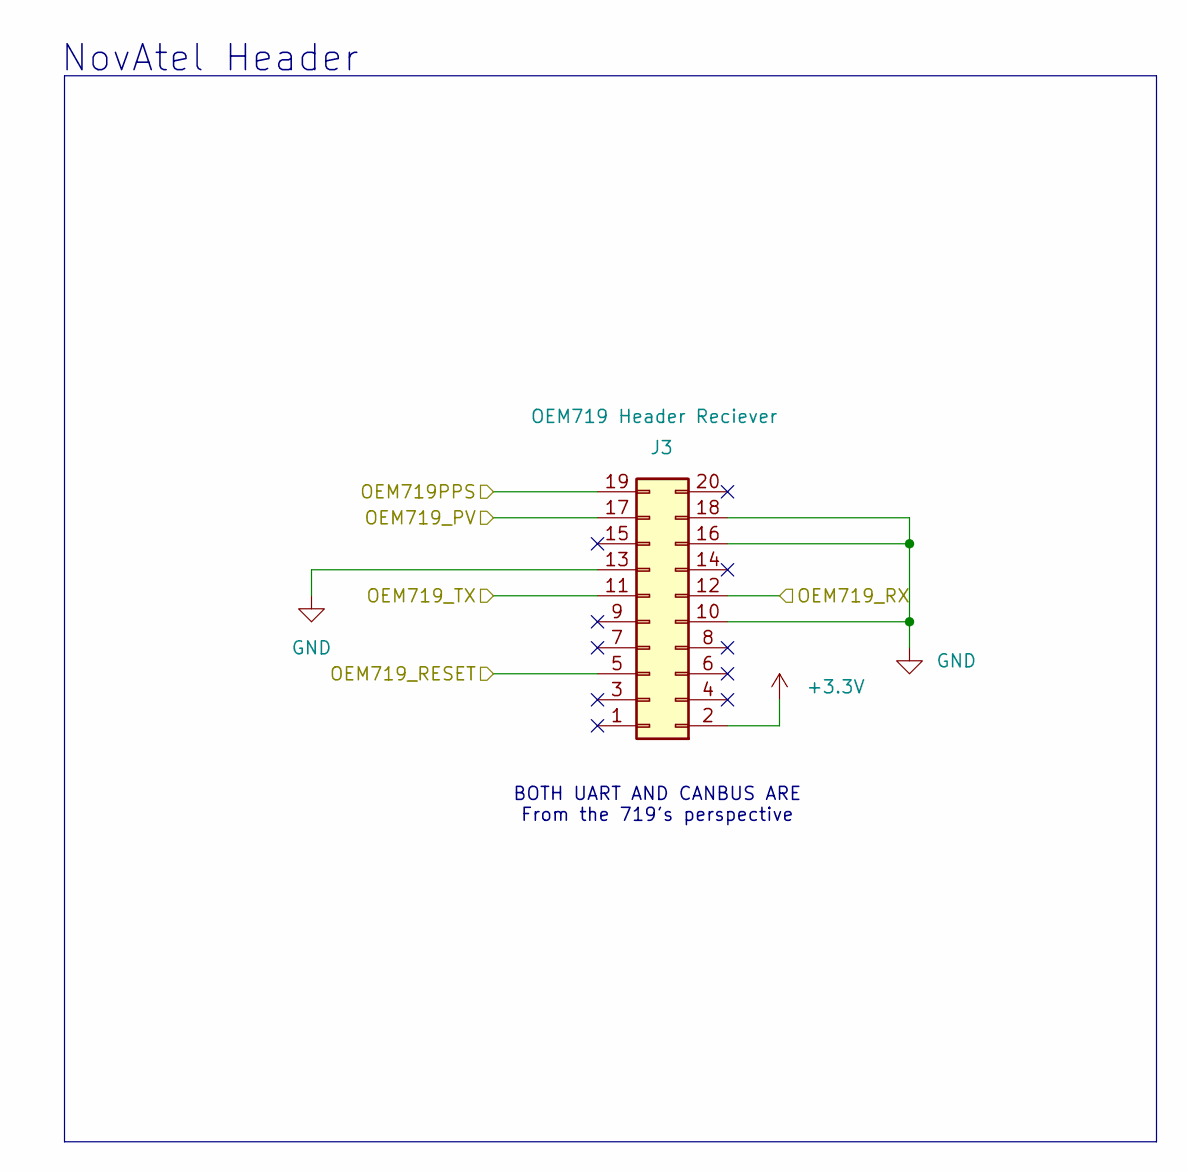
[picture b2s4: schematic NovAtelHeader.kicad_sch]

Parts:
J3: OEM719 Header Reciever

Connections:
unnamed: J3.10 (GND), J3.13 (GND), J3.16 (GND), J3.18 (GND)

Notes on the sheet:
NovAtel Header
BOTH UART AND CANBUS ARE From the 719's perspective

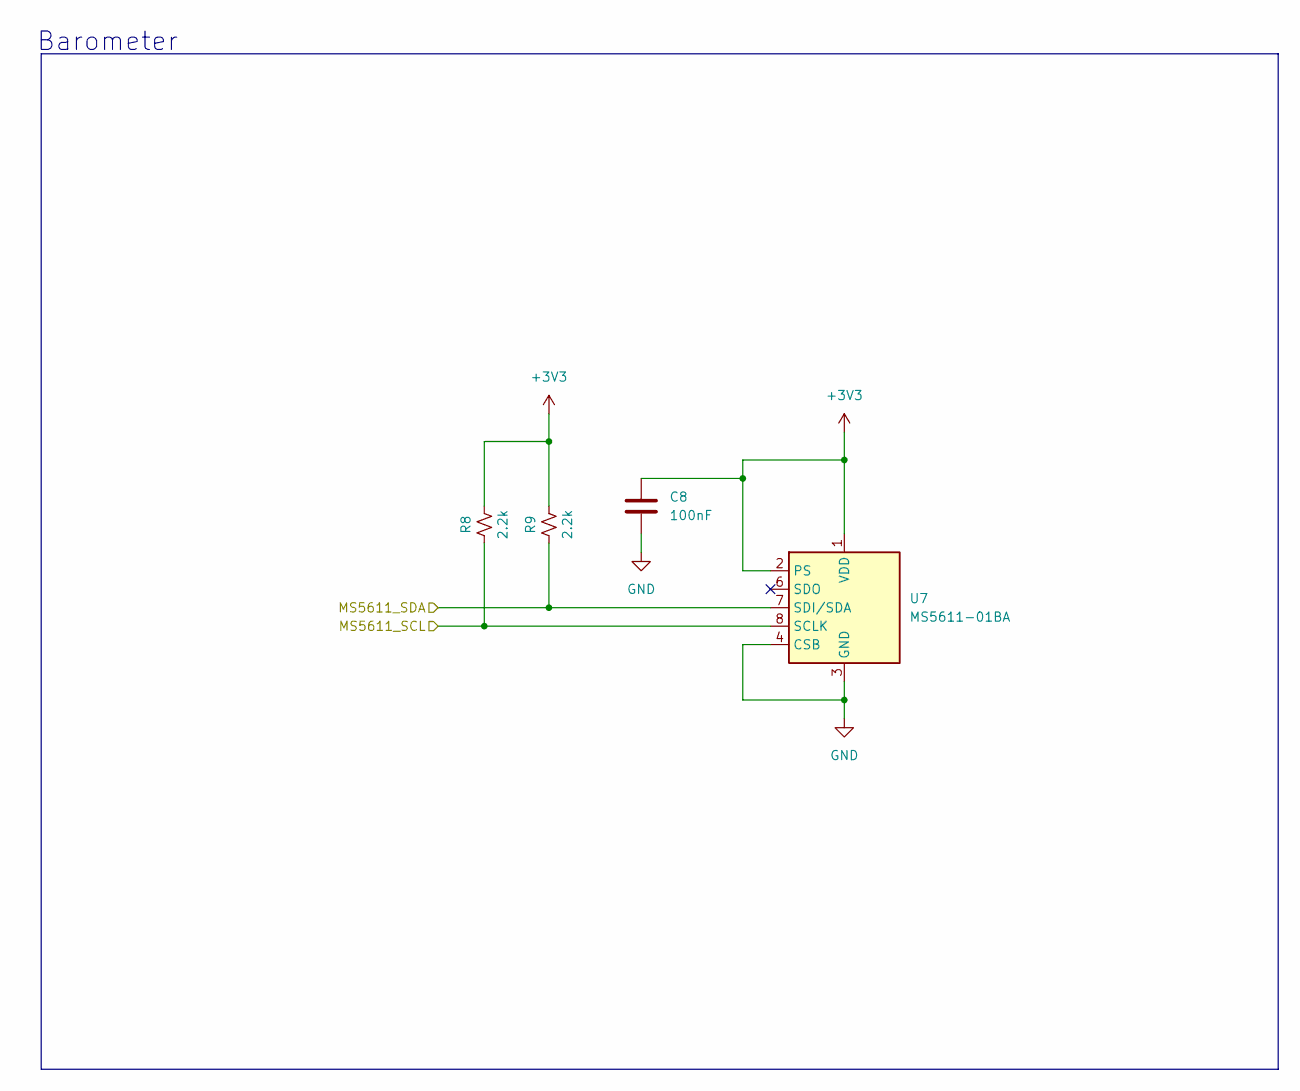
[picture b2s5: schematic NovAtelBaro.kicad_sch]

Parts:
C8: 100nF; C_0603_1608Metric_Pad1.08x0.95mm_HandSolder
R8, R9: 2.2k; R_0402_1005Metric; LCSC Part # C144773
U7: MS5611-01BA; LGA-8_3x5mm_P1.25mm

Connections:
+3V3: C8.1, R8.1, R9.1, U7.1 (VDD), U7.2 (PS); also elsewhere on the board
/NovAtelBaro/MS5611_SCL: R8.2, U7.8 (SCLK); also elsewhere on the board
/NovAtelBaro/MS5611_SDA: R9.2, U7.7 (SDI/SDA); also elsewhere on the board
GND: C8.2, U7.3 (GND), U7.4 (CSB), U7.5 (CSB); also elsewhere on the board

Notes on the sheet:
Barometer
